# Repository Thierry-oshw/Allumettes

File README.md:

# Allumettes
module 5mm x 34mm de fonction unitaire

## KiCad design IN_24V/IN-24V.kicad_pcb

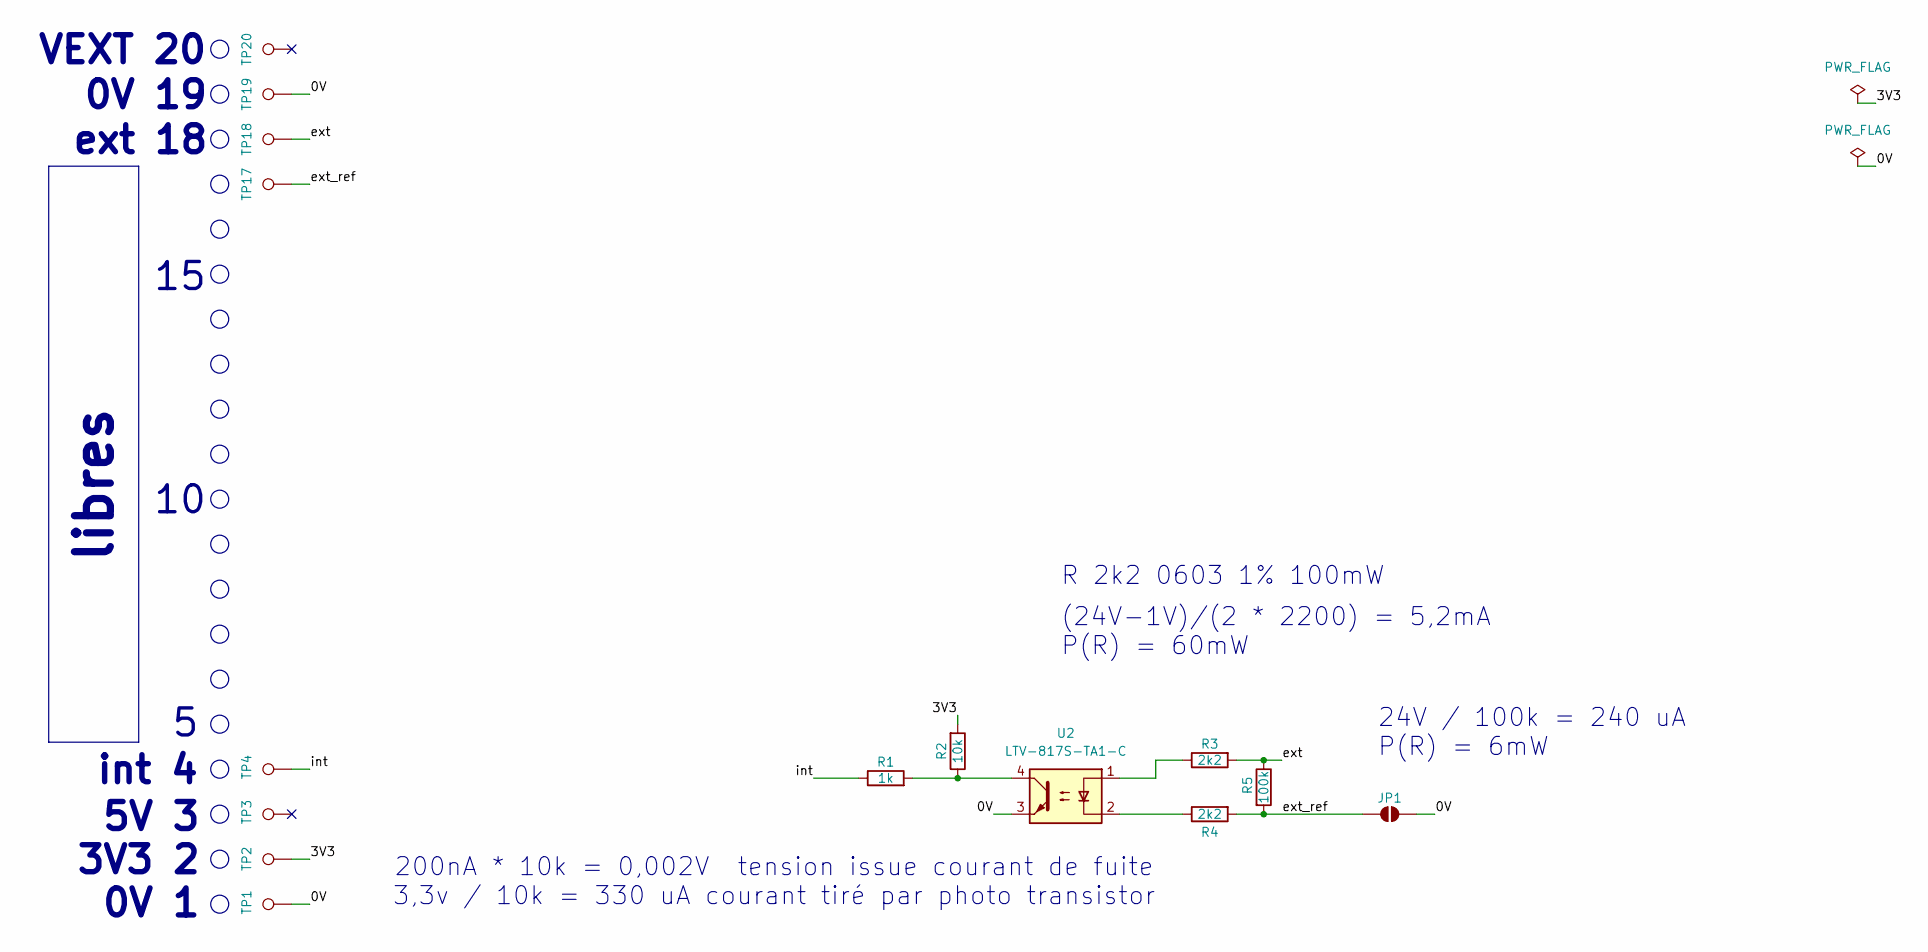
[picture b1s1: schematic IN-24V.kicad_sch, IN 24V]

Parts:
JP1: SolderJumper_2_Open; SolderJumper-2_P1.3mm_Open_TrianglePad1.0x1.5mm
R1: 1k; R_0603_1608Metric; LCSC C21190
R2: 10k; R_0603_1608Metric; LCSC C25804
R3, R4: 2k2; R_0603_1608Metric; LCSC C4190
R5: 100k; R_0603_1608Metric; LCSC C25803
TP1, TP2, TP3, TP4, TP17, TP18, TP19, TP20: TestPoint; Pastille
U2: LTV-817S-TA1-C; SMDIP-4_W9.53mm; LCSC C109227

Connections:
/0V: JP1.2 (B), TP1.1, TP19.1, U2.3
/3V3: R2.2, TP2.1
/ext: R3.2, R5.1, TP18.1
/ext_ref: JP1.1 (A), R4.2, R5.2, TP17.1
/int: R1.1, TP4.1
unnamed: R1.2, R2.1, U2.4
unnamed: R3.1, U2.1
unnamed: R4.1, U2.2

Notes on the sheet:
(24V-1V)/(2 * 2200) = 5,2mA P(R) = 60mW
R 2k2 0603 1% 100mW
0V 19
3V3 2
ext 18
0V 1
int 4
VEXT 20
5V 3
200nA * 10k = 0,002V tension issue courant de fuite 3,3v / 10k = 330 uA courant tiré par photo transistor
libres
24V / 100k = 240 uA P(R) = 6mW

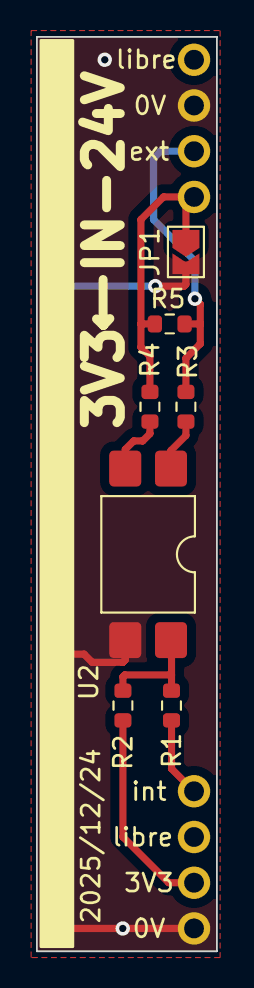
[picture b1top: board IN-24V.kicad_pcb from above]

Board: 2 copper layers, 10.0 x 50.8 mm, 15 parts (0 on the bottom side), 8 nets.

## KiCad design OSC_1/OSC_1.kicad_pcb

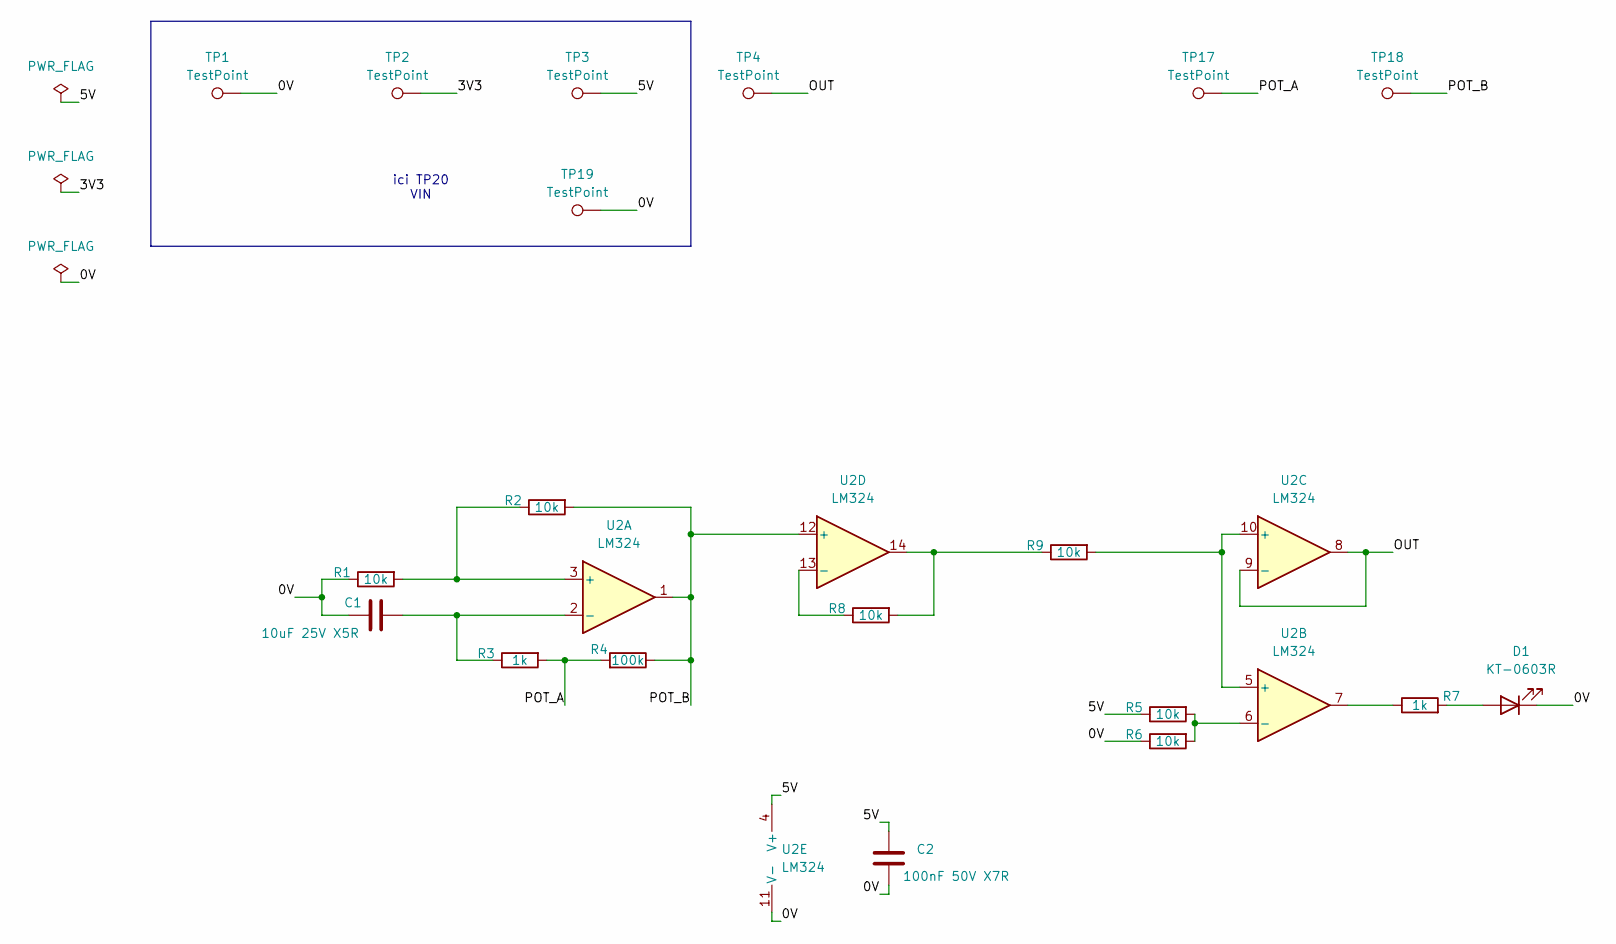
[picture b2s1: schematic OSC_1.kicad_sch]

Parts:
C1: 10uF 25V X5R; C_0805_2012Metric; LCSC C15850
C2: 100nF 50V X7R; C_0603_1608Metric; LCSC C14663
D1: KT-0603R; LED_0603_1608Metric; LCSC C2286
R1, R2, R5, R6, R8, R9: 10k; R_0603_1608Metric; LCSC C25804
R3, R7: 1k; R_0603_1608Metric; LCSC C21190
R4: 100k; R_0603_1608Metric; LCSC C25803
TP1, TP2, TP3, TP4, TP17, TP18, TP19: TestPoint; Pastille
U2: LM324; SOIC-14_3.9x8.7mm_P1.27mm; LCSC C71035

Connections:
/0V: C1.2, C2.2, D1.1 (K), R1.1, R6.1, TP1.1, TP19.1, U2.11 (V-)
/3V3: TP2.1
/5V: C2.1, R5.1, TP3.1, U2.4 (V+)
/OUT: TP4.1, U2.8, U2.9 (-)
/POT_A: R3.2, R4.2, TP17.1
/POT_B: R2.2, R4.1, TP18.1, U2.1, U2.12 (+)
unnamed: D1.2 (A), R7.2
unnamed: R7.1, U2.7
unnamed: R8.2, R9.1, U2.14
unnamed: R1.2, R2.1, U2.3 (+)
unnamed: C1.1, R3.1, U2.2 (-)
unnamed: R9.2, U2.5 (+), U2.10 (+)
unnamed: R5.2, R6.2, U2.6 (-)
unnamed: R8.1, U2.13 (-)

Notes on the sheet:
ici TP20 VIN

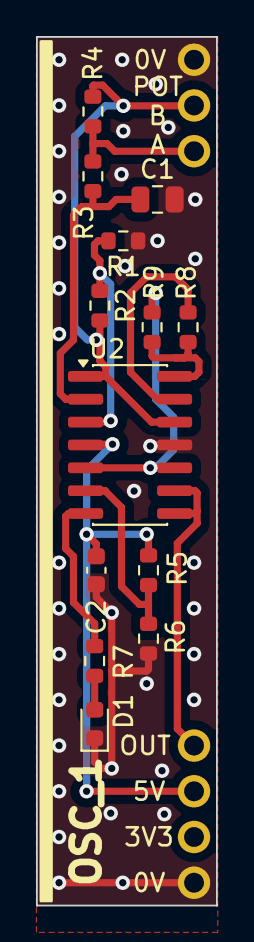
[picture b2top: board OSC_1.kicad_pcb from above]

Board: 2 copper layers, 10.0 x 48.3 mm, 20 parts (0 on the bottom side), 13 nets.

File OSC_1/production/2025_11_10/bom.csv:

Designator,Footprint,Quantity,Value,LCSC Part #
C1,0805,1,10uF 25V X5R,C15850
C2,0603,1,100nF 50V X7R,C14663
D1,0603,1,KT-0603R,C2286
"R1, R2, R5, R6, R8, R9",0603,6,10k,C25804
"R3, R7",0603,2,1k,C21190
R4,0603,1,100k,C25803
U2,SOIC-14_3.9x8.7mm_P1.27mm,1,LM324,C71035

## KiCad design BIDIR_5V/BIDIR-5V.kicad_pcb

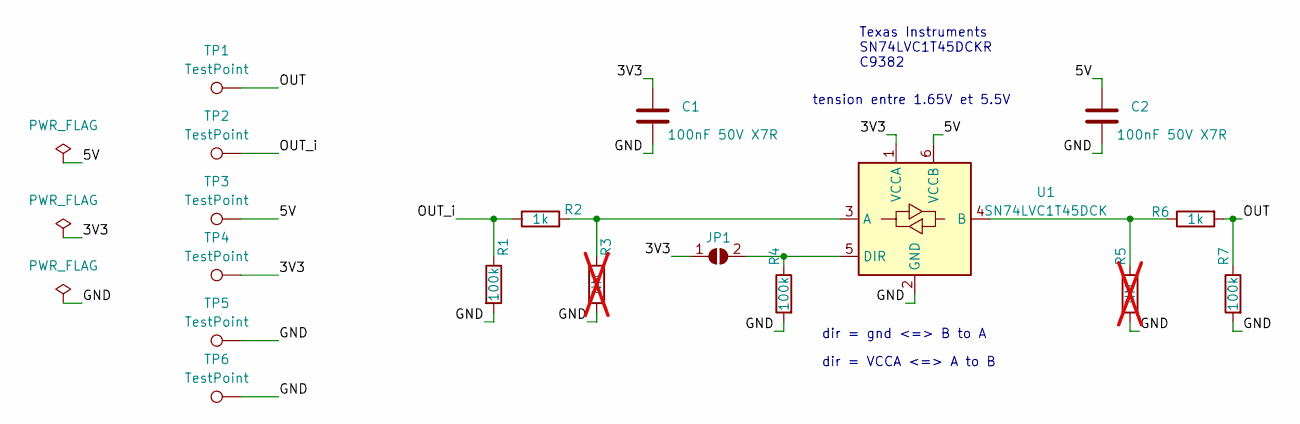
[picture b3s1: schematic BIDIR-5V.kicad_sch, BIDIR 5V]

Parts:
C1, C2: 100nF 50V X7R; C_0603_1608Metric; LCSC C14663
JP1: SolderJumper_2_Open; SolderJumper-2_P1.3mm_Open_TrianglePad1.0x1.5mm
R1, R4, R7: 100k; R_0603_1608Metric; LCSC C25803
R2, R6: 1k; R_0603_1608Metric; LCSC C21190
R3, R5: NM; R_0603_1608Metric; not fitted
TP1, TP2, TP3, TP4, TP5, TP6: TestPoint; Pastille
U1: SN74LVC1T45DCK; SOT-363_SC-70-6; LCSC C9382

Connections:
/3V3: C1.1, JP1.1 (A), TP4.1, U1.1 (VCCA)
/5V: C2.1, TP3.1, U1.6 (VCCB)
/GND: C1.2, C2.2, R1.2, R3.2, R4.2, R5.2, R7.2, TP5.1, TP6.1, U1.2 (GND)
/OUT: R6.2, R7.1, TP1.1
/OUT_i: R1.1, R2.1, TP2.1
unnamed: JP1.2 (B), R4.1, U1.5 (DIR)
unnamed: R2.2, R3.1, U1.3 (A)
unnamed: R5.1, R6.1, U1.4 (B)

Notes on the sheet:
Texas Instruments SN74LVC1T45DCKR C9382
tension entre 1.65V et 5.5V
dir = VCCA <=> A to B
dir = gnd <=> B to A

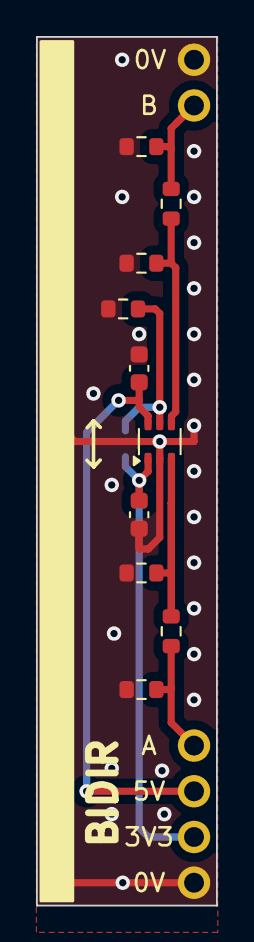
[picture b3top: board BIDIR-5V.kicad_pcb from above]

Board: 2 copper layers, 10.0 x 48.3 mm, 17 parts (1 on the bottom side), 8 nets.

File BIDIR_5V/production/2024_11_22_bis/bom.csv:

Designator,Footprint,Quantity,Value,LCSC Part #
"C1, C2",0603,2,100nF 50V X7R,C14663
"R1, R4, R7",0603,3,100k,C25803
"R2, R6",0603,2,1k,C21190
U1,SOT-363_SC-70-6,1,SN74LVC1T45DCK,C9382

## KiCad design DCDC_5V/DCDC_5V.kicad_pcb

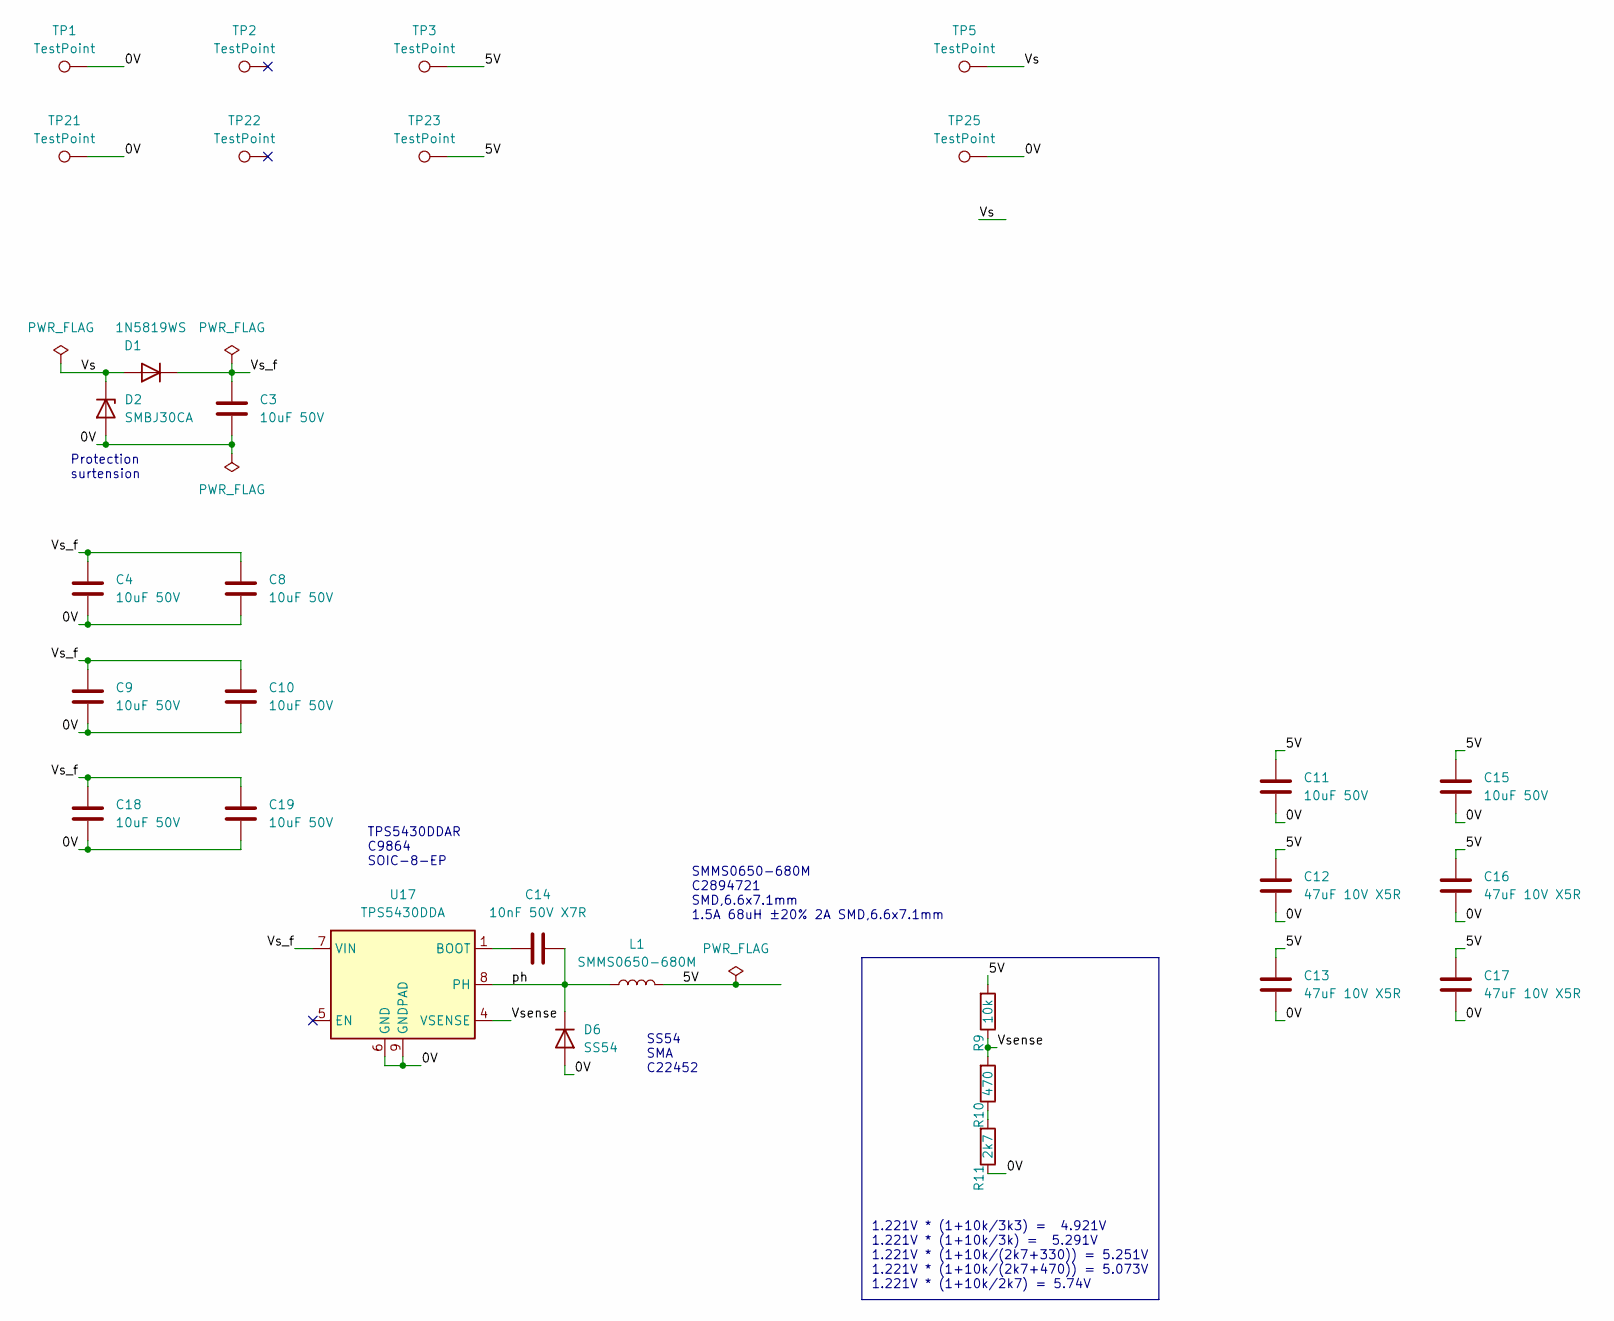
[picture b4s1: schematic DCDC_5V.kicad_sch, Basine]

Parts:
C3, C4, C8, C9, C10, C11, C15, C18, C19: 10uF 50V; C_1206_3216Metric; LCSC C13585
C12, C13, C16, C17: 47uF 10V X5R; C_1206_3216Metric; LCSC C96123
C14: 10nF 50V X7R; C_0603_1608Metric; LCSC C57112
D1: 1N5819WS; D_SOD-323; LCSC C191023
D2: SMBJ30CA; D_SMB; LCSC C2925441
D6: SS54; D_SMA; LCSC C22452
L1: SMMS0650-680M; L_Chilisin_BMRB00060650; LCSC C2894721
R9: 10k; R_0603_1608Metric; LCSC C25804
R10: 470; R_0603_1608Metric; LCSC C23179
R11: 2k7; R_0603_1608Metric; LCSC C13167
TP1, TP2, TP3, TP5, TP21, TP22, TP23, TP25: TestPoint; Pastille
U17: TPS5430DDA; TI_SO-PowerPAD-8_ThermalVias; LCSC C9864

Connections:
/0V: C3.2, C4.2, C8.2, C9.2, C10.2, C11.2, C12.2, C13.2, C15.2, C16.2, C17.2, C18.2, C19.2, D2.2 (A), D6.2 (A), R11.1, TP1.1, TP21.1, TP25.1, U17.6 (GND), U17.9 (GNDPAD)
/5V: C11.1, C12.1, C13.1, C15.1, C16.1, C17.1, L1.2, R9.2, TP3.1, TP23.1
/Vs: D1.2 (A), D2.1 (K), TP5.1
/Vs_f: C3.1, C4.1, C8.1, C9.1, C10.1, C18.1, C19.1, D1.1 (K), U17.7 (VIN)
/Vsense: R9.1, R10.2, U17.4 (VSENSE)
/ph: C14.2, D6.1 (K), L1.1, U17.8 (PH)
unnamed: R10.1, R11.2
unnamed: C14.1, U17.1 (BOOT)

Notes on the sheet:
Protection surtension
SMMS0650-680M C2894721 SMD,6.6x7.1mm 1.5A 68uH ±20% 2A SMD,6.6x7.1mm
1.221V * (1+10k/3k3) = 4.921V 1.221V * (1+10k/3k) = 5.291V 1.221V * (1+10k/(2k7+330)) = 5.251V 1.221V * (1+10k/(2k7+470)) = 5.073V 1.221V * (1+10k/2k7) = 5.74V
SS54 SMA C22452
TPS5430DDAR C9864 SOIC-8-EP

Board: 2 copper layers, 30 parts (0 on the bottom side), 8 nets, no tracks yet.

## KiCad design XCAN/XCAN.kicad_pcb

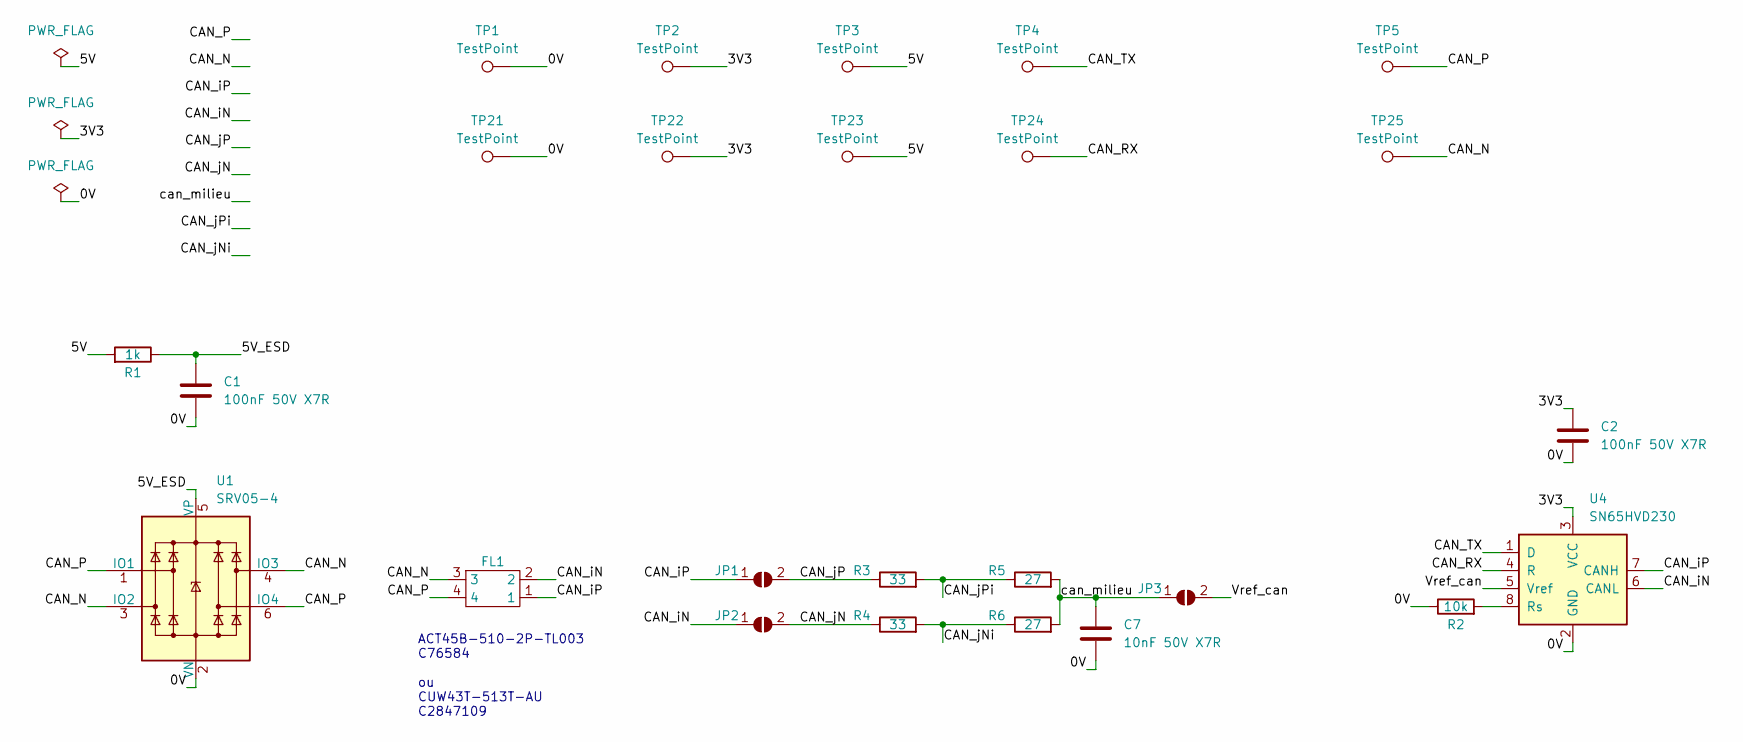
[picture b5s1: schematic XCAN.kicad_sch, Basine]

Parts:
C1, C2: 100nF 50V X7R; C_0603_1608Metric; LCSC C14663
C7: 10nF 50V X7R; C_0603_1608Metric; LCSC C57112
FL1: ACT45B1012PTL003; LCSC C76584
JP1, JP2, JP3: SolderJumper_2_Open; SolderJumper-2_P1.3mm_Open_TrianglePad1.0x1.5mm
R1: 1k; R_0603_1608Metric; LCSC C21190
R2: 10k; R_0603_1608Metric; LCSC C25804
R3, R4: 33; R_0603_1608Metric; LCSC C23140
R5, R6: 27; R_0603_1608Metric; LCSC C25190
TP1, TP2, TP3, TP4, TP5, TP21, TP22, TP23, TP24, TP25: TestPoint; Pastille
U1: SRV05-4; SOT-23-6; LCSC C85364
U4: SN65HVD230; SOIC-8_3.9x4.9mm_P1.27mm; LCSC C12084

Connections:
/0V: C1.2, C2.2, C7.2, R2.1, TP1.1, TP21.1, U1.2 (VN), U4.2 (GND)
/3V3: C2.1, TP2.1, TP22.1, U4.3 (VCC)
/5V: R1.2, TP3.1, TP23.1
/5V_ESD: C1.1, R1.1, U1.5 (VP)
/CAN_N: FL1.3, TP25.1, U1.3 (IO2), U1.4 (IO3)
/CAN_P: FL1.4, TP5.1, U1.1 (IO1), U1.6 (IO4)
/CAN_RX: TP24.1, U4.4 (R)
/CAN_TX: TP4.1, U4.1 (D)
/CAN_iN: FL1.2, JP2.1 (A), U4.6 (CANL)
/CAN_iP: FL1.1, JP1.1 (A), U4.7 (CANH)
/CAN_jN: JP2.2 (B), R4.1
/CAN_jNi: R4.2, R6.1
/CAN_jP: JP1.2 (B), R3.1
/CAN_jPi: R3.2, R5.1
/Vref_can: JP3.2 (B), U4.5 (Vref)
/can_milieu: C7.1, JP3.1 (A), R5.2, R6.2
unnamed: R2.2, U4.8 (Rs)

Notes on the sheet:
ACT45B-510-2P-TL003 C76584 ou CUW43T-513T-AU C2847109

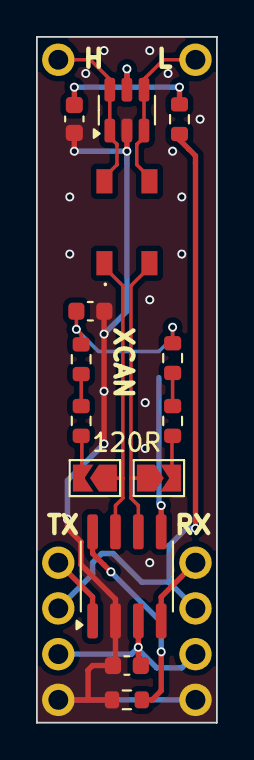
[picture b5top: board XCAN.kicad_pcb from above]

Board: 2 copper layers, 10.0 x 38.1 mm, 25 parts (1 on the bottom side), 17 nets.

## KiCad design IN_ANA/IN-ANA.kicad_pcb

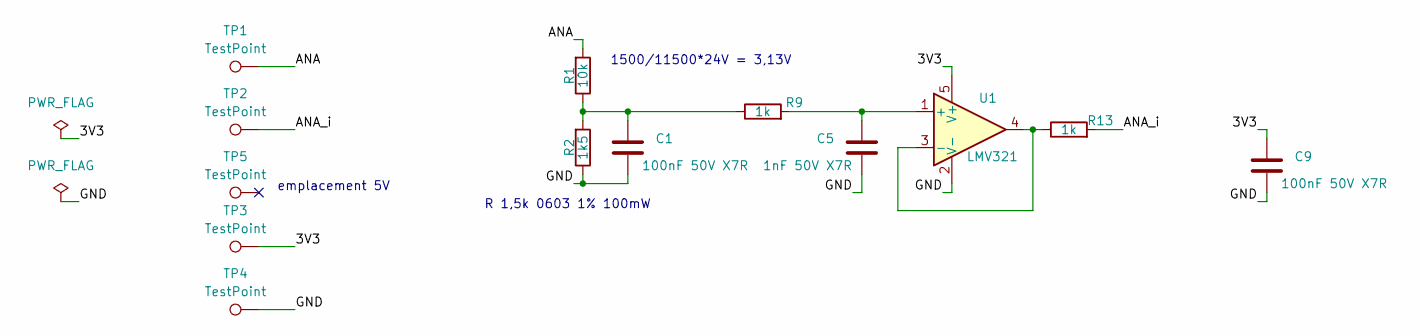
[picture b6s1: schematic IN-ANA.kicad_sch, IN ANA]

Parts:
C1, C9: 100nF 50V X7R; C_0603_1608Metric; LCSC C14663
C5: 1nF 50V X7R; C_0603_1608Metric; LCSC C1588
R1: 10k; R_0603_1608Metric; LCSC C25804
R2: 1k5; R_0603_1608Metric; LCSC C22843
R9, R13: 1k; R_0603_1608Metric; LCSC C21190
TP1, TP2, TP3, TP4, TP5: TestPoint; Pastille
U1: LMV321; SOT-23-5; LCSC C7972

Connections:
/3V3: C9.1, TP3.1, U1.5 (V+)
/ANA: R1.2, TP1.1
/ANA_i: R13.2, TP2.1
/GND: C1.2, C5.2, C9.2, R2.1, TP4.1, U1.2 (V-)
unnamed: C1.1, R1.1, R2.2, R9.1
unnamed: C5.1, R9.2, U1.1 (+)
unnamed: R13.1, U1.3 (-), U1.4

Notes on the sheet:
R 1,5k 0603 1% 100mW
1500/11500*24V = 3,13V
emplacement 5V

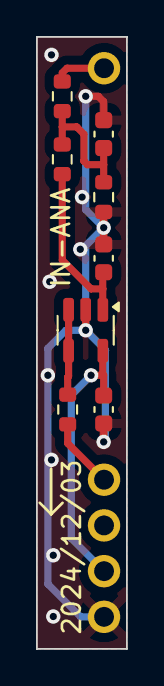
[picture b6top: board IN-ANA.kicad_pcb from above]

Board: 2 copper layers, 5.0 x 34.0 mm, 13 parts (0 on the bottom side), 7 nets.

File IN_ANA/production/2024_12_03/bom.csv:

Designator,Footprint,Quantity,Value,LCSC Part #
"C1, C9",0603,2,100nF 50V X7R,C14663
C5,0603,1,1nF 50V X7R,C1588
R1,0603,1,10k,C25804
"R13, R9",0603,2,1k,C21190
R2,0603,1,1k5,C22843
U1,SOT-23-5,1,LMV321,C7972

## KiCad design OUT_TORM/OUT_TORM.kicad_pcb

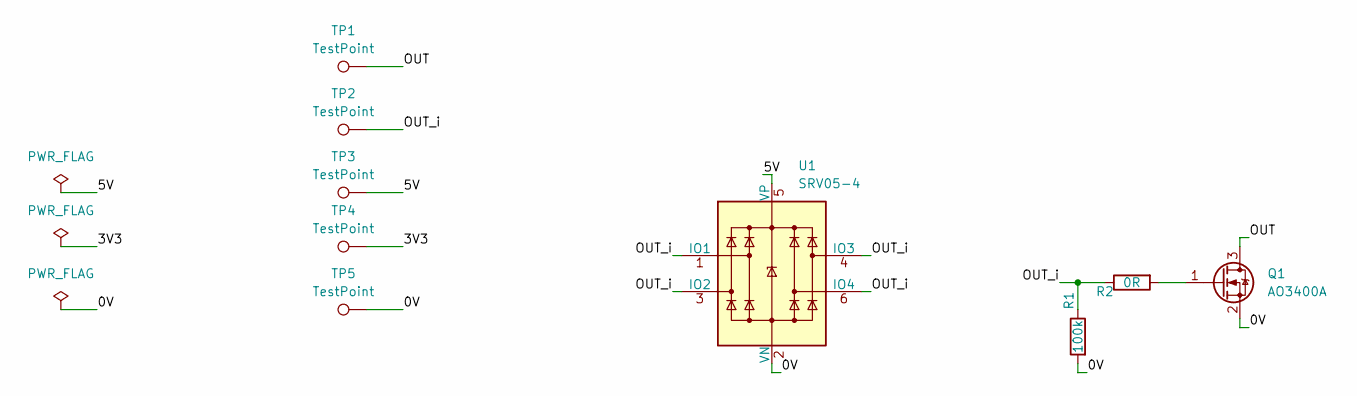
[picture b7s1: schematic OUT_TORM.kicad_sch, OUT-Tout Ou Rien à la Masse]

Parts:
Q1: AO3400A; SOT-23; LCSC C20917
R1: 100k; R_0603_1608Metric; LCSC C25803
R2: 0R; R_0603_1608Metric; LCSC C21189
TP1, TP2, TP3, TP4, TP5: TestPoint; Pastille
U1: SRV05-4; SOT-23-6; LCSC C85364

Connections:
/0V: Q1.2 (S), R1.2, TP5.1, U1.2 (VN)
/3V3: TP4.1
/5V: TP3.1, U1.5 (VP)
/OUT: Q1.3 (D), TP1.1
/OUT_i: R1.1, R2.1, TP2.1, U1.1 (IO1), U1.3 (IO2), U1.4 (IO3), U1.6 (IO4)
unnamed: Q1.1 (G), R2.2

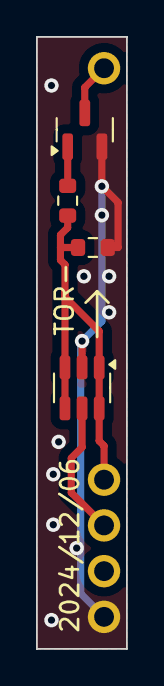
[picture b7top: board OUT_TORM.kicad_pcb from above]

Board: 2 copper layers, 5.0 x 34.0 mm, 9 parts (0 on the bottom side), 5 nets.

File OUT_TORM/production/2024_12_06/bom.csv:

Designator,Footprint,Quantity,Value,LCSC Part #
Q1,SOT-23,1,AO3400A,C20917
R1,0603,1,100k,C25803
R2,0603,1,0R,C21189
U1,SOT-23-6,1,SRV05-4,C85364
